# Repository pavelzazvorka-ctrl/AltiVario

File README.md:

# AltiVario

AltiVario je vario na paragliding. meri a zobrazuje rychlost stoupani/klesani, vysku a posila data pres BT do aplikace XC track na mobilnim telefonu

### Historie:

Cilem hry bylo mit rychle a presne zalozni vario s moznosti exportu zivych dat do aplikace XC track v mobilnim telefonu.
cela akce byla zaroven test mych moznosti a schopnosti zajistit kompletni short-run vyrobu jak HW tak SW. Vyrobil 
jsem celkem deset kusu, ktere jsem vetsinou rozdal znamym. AltiVario opravdu letalo a bylo prakticky pouzitelne.

### HW

vario je postavene nad ESP32 a nejlepsim barometrickym sensorem na trhu MSI5611.Duraz byl kladen hlavne na minimalni
prodlevu a presnost. Soucasti repository jsou i data pro vyrobu PCB ( Eagle ) a CNC G-code data pro frezovani krabicek 
a duralovych ramecku.

Vyvoj byl uspesny, vyroba byla rozumne automatizovana, finalni cena jednoho kusu byla kolem 600 CZK ( viz xls ) 

### SW

Popis SW a celkove ovladani pristore je popsano v Vario.md

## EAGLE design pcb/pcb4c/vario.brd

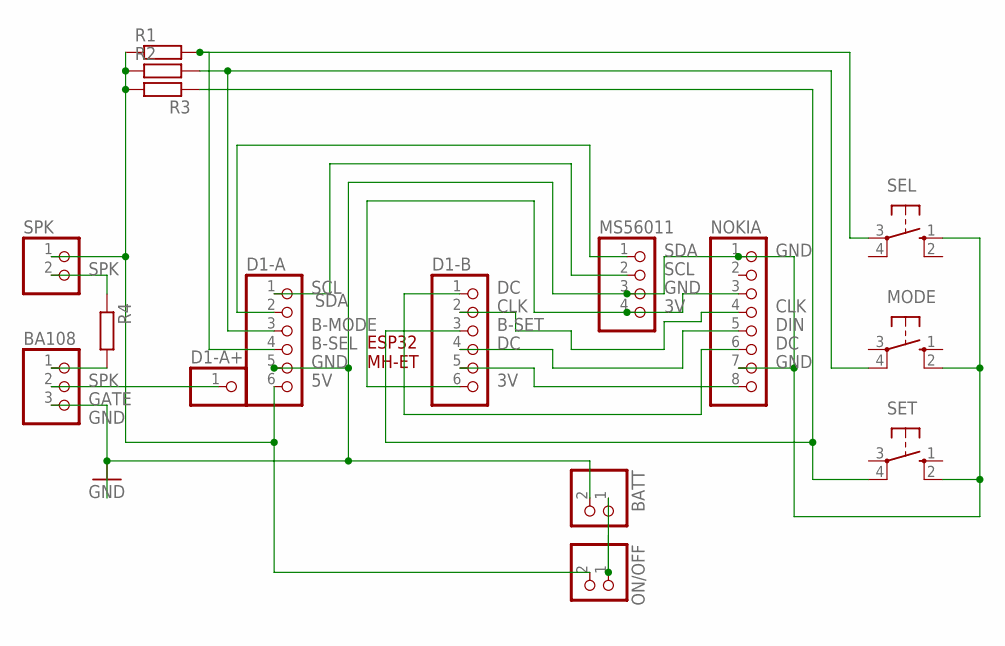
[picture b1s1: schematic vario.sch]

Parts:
BA108: PINHD-1X3; 1X03
BATT: PINHD-1X2; 1X02
D1-A, D1-B: PINHD-1X6; 1X06
D1-A+: PINHD-1X1; 1X01
MODE: 10-XX; B3F-10XX
MS56011: PINHD-1X4; 1X04
NOKIA: PINHD-1X8; 1X08
ON/OFF: PINHD-1X2; 1X02
R1, R2, R3, R4: R-EU_0207/10; 0207/10
SEL: 10-XX; B3F-10XX
SET: 10-XX; B3F-10XX
SPK: PINHD-1X2; 1X02

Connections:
3V: D1-B.6, MS56011.4, NOKIA.3
5V: D1-A.6, ON/OFF.2, R1.1, R2.1, R3.2, SPK.1
B-MODE: D1-A.3, MODE.4 (P1), R2.2
B-SEL: D1-A.4, R1.2, SEL.3
B-SET: D1-B.3, R3.1, SET.4 (P1)
BATT: BATT.1, ON/OFF.1
CLK: D1-B.2, NOKIA.4
DC: D1-B.1, NOKIA.6
DIN: D1-B.4, NOKIA.5
GATE: BA108.2, D1-A+.1
GND: BA108.3, BATT.2, D1-A.5, MODE.2 (S1), MS56011.3, NOKIA.1, NOKIA.7, SEL.1 (S), SET.2 (S1)
unnamed: R4.1, SPK.2
RST: D1-B.5, NOKIA.8
SCL: D1-A.1, MS56011.2
SDA: D1-A.2, MS56011.1
SPK: BA108.1, R4.2

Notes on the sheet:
ESP32 MH-ET

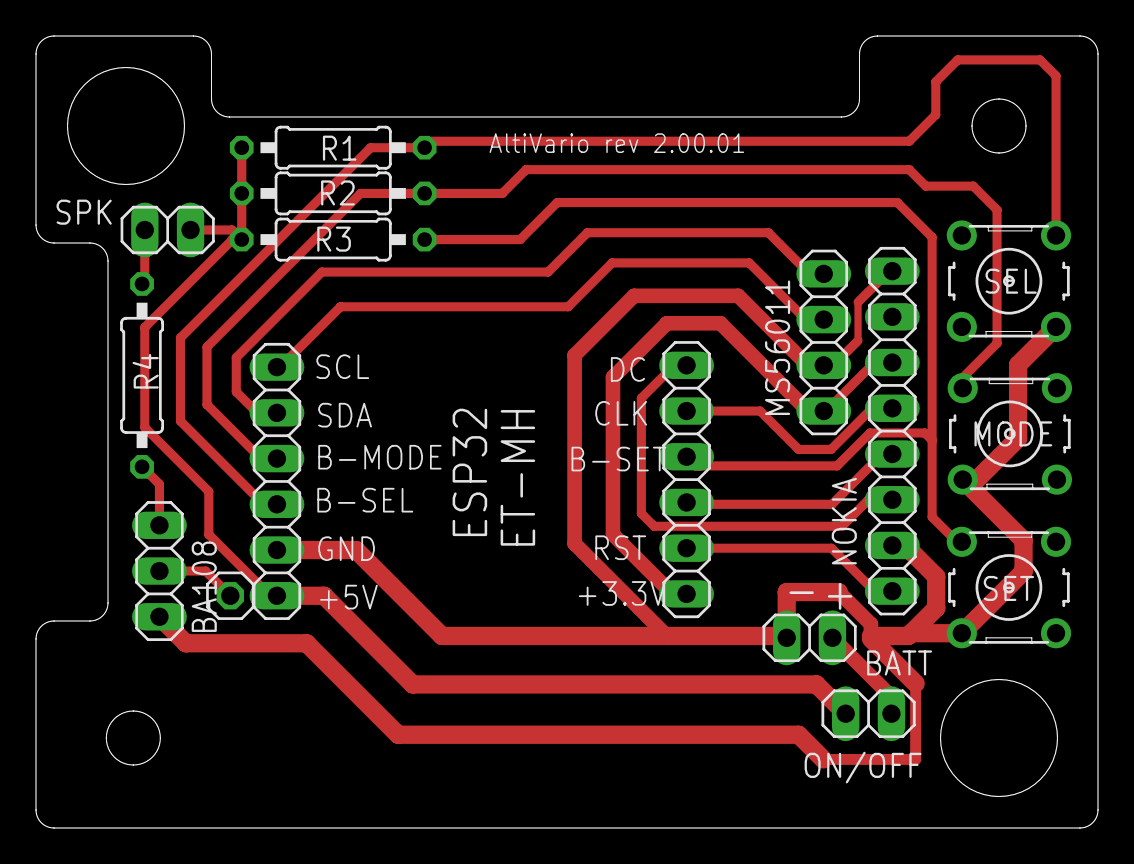
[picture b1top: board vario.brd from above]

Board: 2 copper layers, 59.0 x 44.0 mm, 16 parts (0 on the bottom side), 16 nets.
